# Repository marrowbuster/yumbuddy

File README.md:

# yumbuddy
tiny lil' esp32-c6 based wireless development board designed for the flipper zero. only takes up one set of gpio pins!

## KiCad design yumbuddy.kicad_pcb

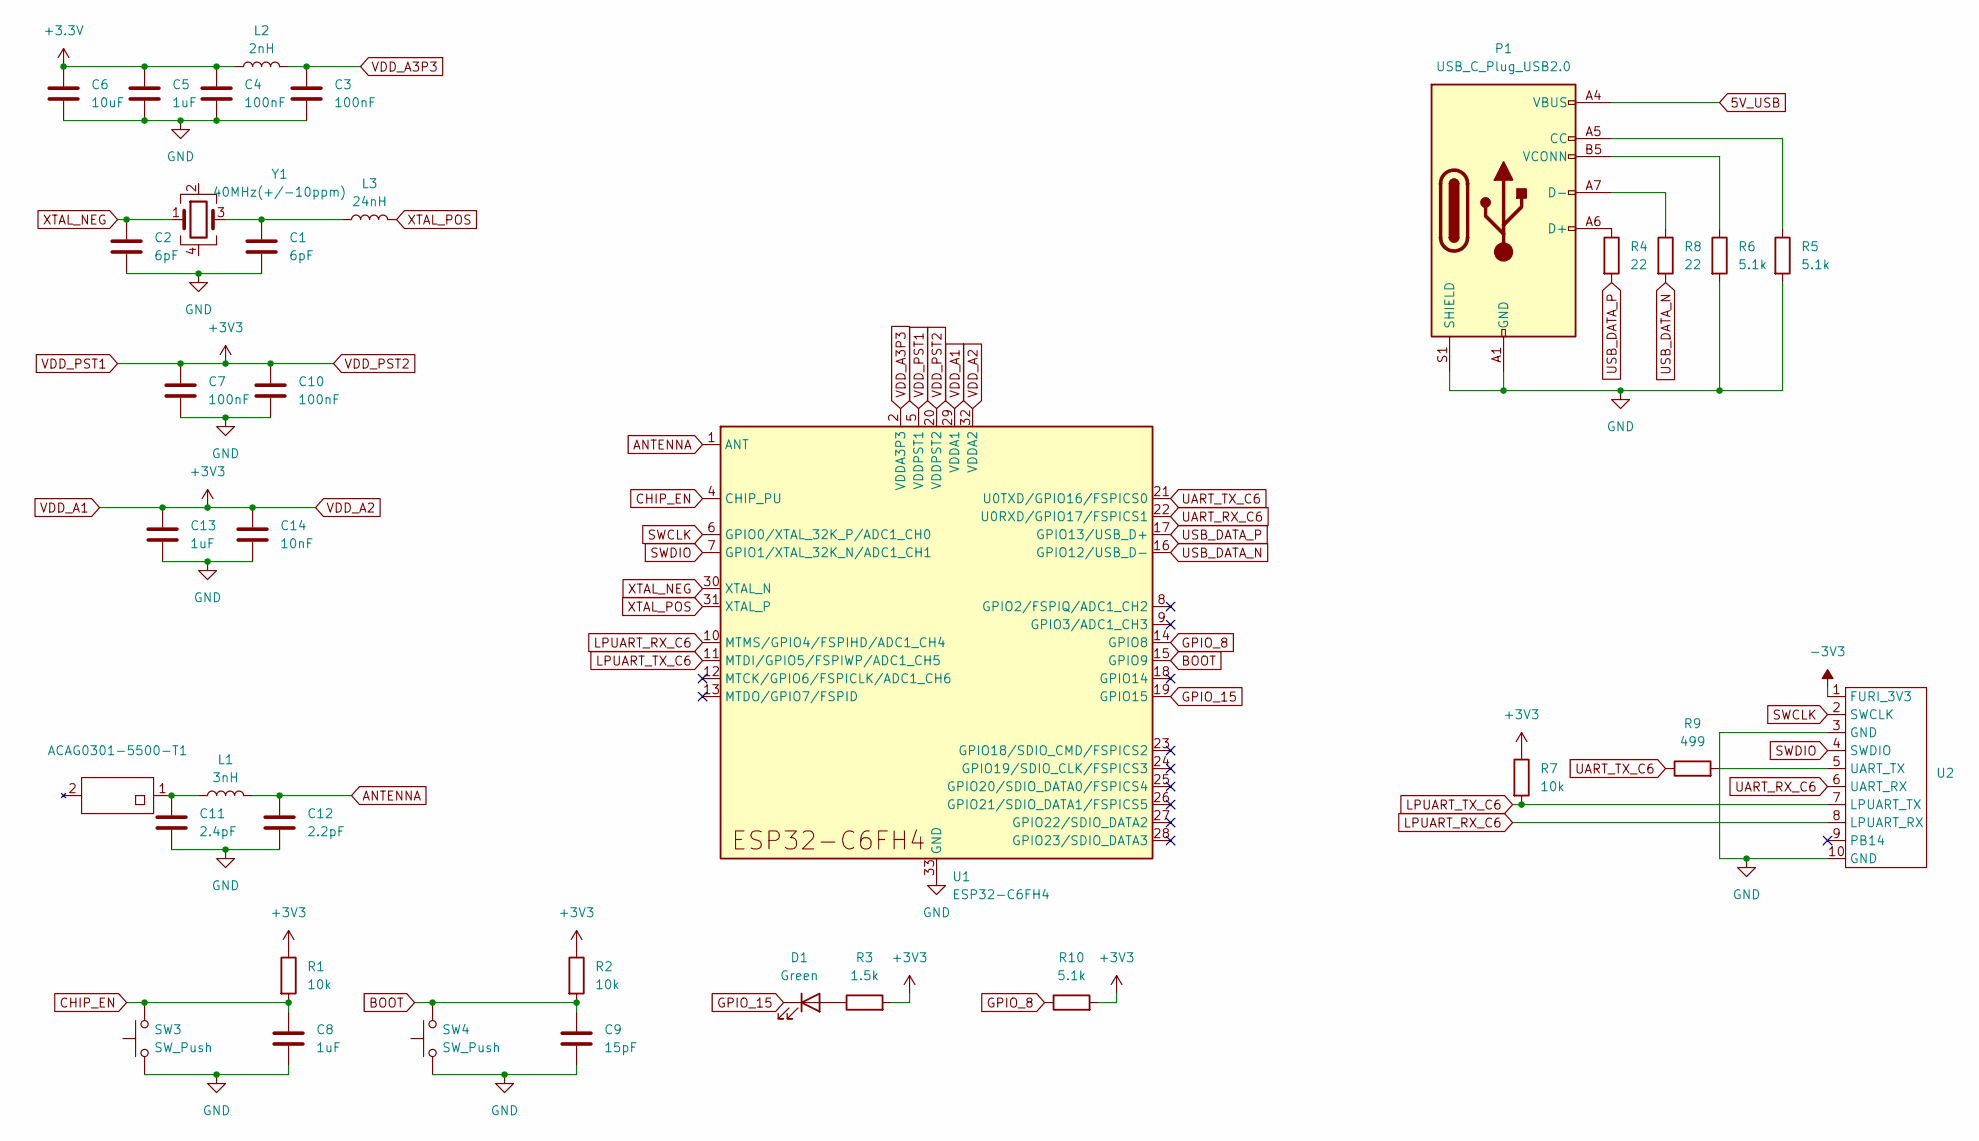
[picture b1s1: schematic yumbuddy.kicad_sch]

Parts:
ACAG0301-5500-T1: Johanson_2450AT43F0100
C1, C2: 6pF; R_0603_1608Metric
C3, C4, C7, C10: 100nF; R_0603_1608Metric
C5, C8, C13: 1uF; R_0603_1608Metric
C6: 10uF; R_0603_1608Metric
C9: 15pF; R_0603_1608Metric
C11: 2.4pF; R_0603_1608Metric
C12: 2.2pF; R_0603_1608Metric
C14: 10nF; R_0603_1608Metric
D1: Green; LED_0603_1608Metric
L1: 3nH; L_0603_1608Metric
L2: 2nH; L_0603_1608Metric
L3: 24nH; L_0603_1608Metric
P1: USB_C_Plug_USB2.0; USB_C_Receptacle_Amphenol_124019772112A
R1, R2, R7: 10k; R_0603_1608Metric
R3: 1.5k; R_0603_1608Metric
R4, R8: 22; R_0603_1608Metric
R5, R6, R10: 5.1k; R_0603_1608Metric
R9: 499; R_0603_1608Metric
SW3, SW4: SW_Push; SW_Push_SPST_NO_Alps_SKRK
U1: ESP32-C6FH4; QFN-32-1EP_5x5mm_P0.5mm_EP3.6x3.6mm
U2: PinHeader_1x10_P2.54mm_Horizontal
Y1: 40MHz(+/-10ppm); Crystal_SMD_1210-4Pin_1.2x1.0mm

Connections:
5V_USB: P1.A4 (VBUS), P1.A9 (VBUS), P1.B4 (VBUS), P1.B9 (VBUS)
+3.3V: C4.1, C5.1, C6.1, L2.1
-3V3: U2.1 (FURI_3V3)
ANTENNA: C12.1, L1.2, U1.1 (ANT)
BOOT: C9.1, R2.2, SW4.2, U1.15 (GPIO9)
CHIP_EN: C8.1, R1.2, SW3.2, U1.4 (CHIP_PU)
GND: C1.2, C2.2, C3.2, C4.2, C5.2, C6.2, C7.2, C8.2, C9.2, C10.2, C11.2, C12.2, C13.2, C14.2, P1.A1 (GND), P1.A12 (GND), P1.B1 (GND), P1.B12 (GND), P1.S1 (SHIELD), R5.2, R6.2, SW3.1, SW4.1, U1.33 (GND), U2.3 (GND), U2.10 (GND)
GPIO_8: R10.1, U1.14 (GPIO8)
GPIO_15: D1.1 (K), U1.19 (GPIO15)
LPUART_RX_C6: U1.10 (MTMS/GPIO4/FSPIHD/ADC1_CH4), U2.8 (LPUART_RX)
LPUART_TX_C6: R7.2, U1.11 (MTDI/GPIO5/FSPIWP/ADC1_CH5), U2.7 (LPUART_TX)
unnamed: ACAG0301-5500-T1.1, C11.1, L1.1
unnamed: C1.1, L3.1, Y1.3
unnamed: D1.2 (A), R3.1
unnamed: P1.A5 (CC), R5.1
unnamed: P1.A6 (D+), R4.1
unnamed: P1.A7 (D-), R8.1
unnamed: P1.B5 (VCONN), R6.1
unnamed: R9.2, U2.5 (UART_TX)
SWCLK: U1.6 (GPIO0/XTAL_32K_P/ADC1_CH0), U2.2 (SWCLK)
SWDIO: U1.7 (GPIO1/XTAL_32K_N/ADC1_CH1), U2.4 (SWDIO)
UART_RX_C6: U1.22 (U0RXD/GPIO17/FSPICS1), U2.6 (UART_RX)
UART_TX_C6: R9.1, U1.21 (U0TXD/GPIO16/FSPICS0)
USB_DATA_N: R8.2, U1.16 (GPIO12/USB_D-)
USB_DATA_P: R4.2, U1.17 (GPIO13/USB_D+)
VDD_A1: C7.1, C10.1, C13.1, C14.1, R1.1, R2.1, R3.2, R7.1, R10.2, U1.5 (VDDPST1), U1.20 (VDDPST2), U1.29 (VDDA1), U1.32 (VDDA2)
VDD_A3P3: C3.1, L2.2, U1.2 (VDDA3P3), U1.3 (VDDA3P3)
XTAL_NEG: C2.1, U1.30 (XTAL_N), Y1.1
XTAL_POS: L3.2, U1.31 (XTAL_P)

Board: 2 copper layers, 35 parts (0 on the bottom side), 28 nets, no tracks yet.

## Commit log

2025-05-07 initial commit of files
2025-05-07 keep work journal
2025-05-08 component footprint and mapping, update schematics
2025-08-08 save code to Github before operating system change
    The software/hardware architecture of modern Windows gaming laptops has become godawful. It's only going to get worse when you vibe code unoptimised nonsense like React Native UIs.
